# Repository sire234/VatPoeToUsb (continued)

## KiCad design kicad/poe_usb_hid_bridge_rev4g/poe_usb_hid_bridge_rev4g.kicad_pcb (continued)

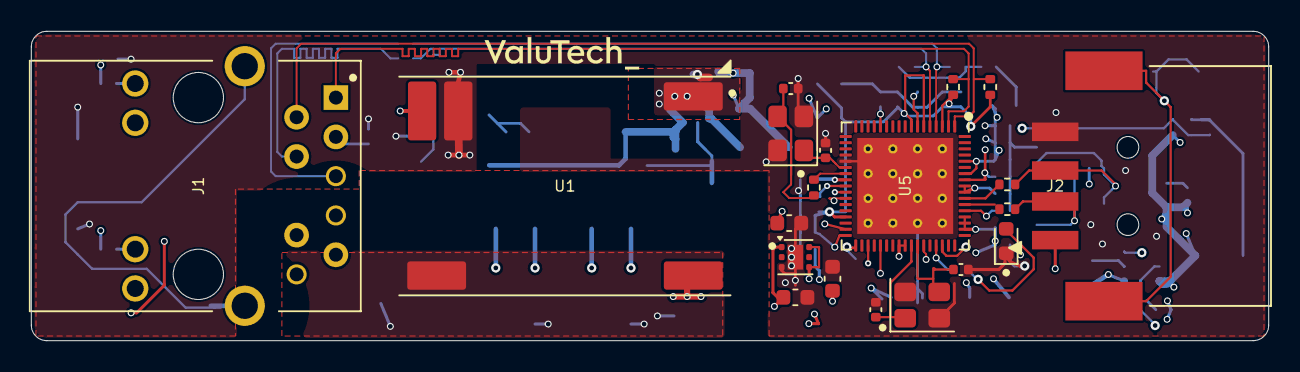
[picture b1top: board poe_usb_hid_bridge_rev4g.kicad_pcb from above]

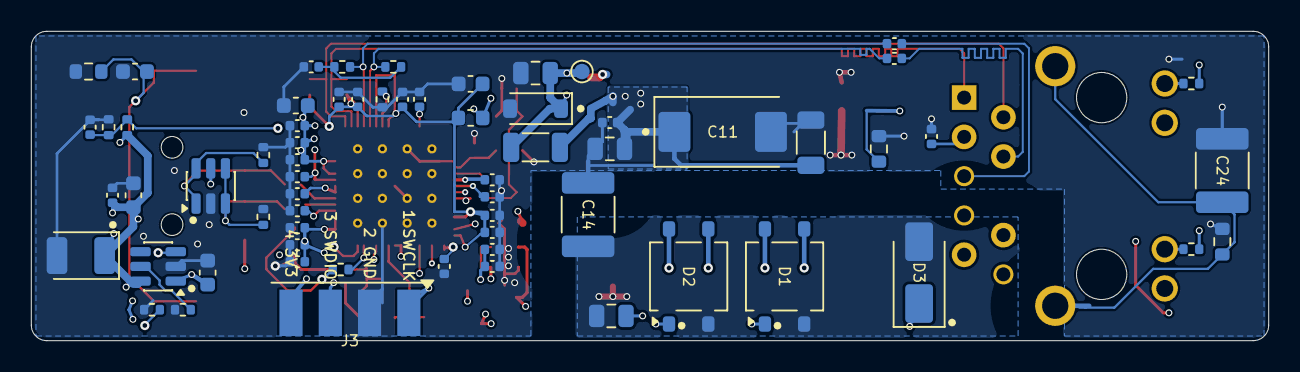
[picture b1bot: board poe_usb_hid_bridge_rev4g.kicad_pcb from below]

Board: 6 copper layers, 80.0 x 20.0 mm, 86 parts (65 on the bottom side), 46 nets.

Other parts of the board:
G1: Logo_ValuTech_10mm

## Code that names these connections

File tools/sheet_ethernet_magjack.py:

"""Wired layout of sheet B1 ethernet_magjack (HR871150C, TX/RX 49.9 R termination, RX coupling
caps C65/C66, CT decoupling, shield R7 || C24, PoE pairs to B2).
Usage: python tools/sheet_ethernet_magjack.py <source project dir (label-only rev4e)> <target project dir>
"""
from sheet_common import open_sheet, finish

s, dst = open_sheet('ethernet_magjack', 1, 'B1 ethernet_magjack – RJ45-MagJack HR871150C',
                    ['PHY-Seite (SEKUNDÄR, links): TX-Paar mit 49,9 Ω an +3V3A (R1/R2); CT an +3V3A (C23)',
                     'RX über Koppel-C C65/C66 6,8 nF (DC-Trennung, WIZnet-Referenz), Terminierung R3/R4 + C21',
                     'Kabelseite (PRIMÄR, rechts): J1.7–J1.10 → PSE_CT12/CT36/SP45/SP78 (zu B2); Schirm über R7 ∥ C24 an GND',
                     'MagJack-LEDs (Rev 4g): grün J1.13/14 = Link ← U5 LINKLED, gelb J1.11/12 = Activity ← U5 ACTLED,',
                     'aktiv low; Anoden über R5/R6 330 Ω an +3V3 (≈ 4 mA)'],
                    frame_size=(233.68, 157.48))

s.place('J1', 177.8, 88.9, 0, ref_at=(-10.16, -15.24), val_at=(-10.16, -12.7))
TXP, TXN, CT, RXP, RXN = 63.5, 71.12, 88.9, 109.22, 124.46
XL = 101.6                                   # left label column

# ---- fan-out of the PHY-side pins into widely spaced rows ----
tdp, tdm, ct = s.pin('J1', 'TD+'), s.pin('J1', 'TD-'), s.pin('J1', 'CT')
rdp, rdm = s.pin('J1', 'RD+'), s.pin('J1', 'RD-')
s.wire(tdp, (157.48, tdp[1]), (157.48, TXP), (XL, TXP))
s.wire(tdm, (154.94, tdm[1]), (154.94, TXN), (XL, TXN))
s.glabel('ETH_TXP', (XL, TXP), angle=180)
s.glabel('ETH_TXN', (XL, TXN), angle=180)

# TX termination: R1 TXP -> +3V3A (up), R2 TXN -> CT row (+3V3A)
s.place('R1', 137.16, TXP - 3.81, 0)
s.wire(s.pin('R1', '1'), (137.16, TXP - 10.16))
s.glabel('+3V3A', (137.16, TXP - 10.16), angle=90)
s.place('R2', 142.24, 77.47, 180)
s.wire((142.24, TXN), s.pin('R2', '2'))
s.wire(s.pin('R2', '1'), (142.24, CT))

# centre tap = +3V3A, decoupled by C23
s.wire(ct, (127.0, CT))
s.glabel('+3V3A', (127.0, CT), angle=180)
s.place('C23', 134.62, CT + 3.81, 0, ref_at=(-5.08, -1.27), val_at=(-5.08, 1.27))
s.power('GND', s.pin('C23', '2'), down=2.54)
s.flag((151.13, CT), up=2.54)

# RX: J1 -> coupling cap -> PHY, termination R3/R4 to ETH_RX_TERM, C21 to GND
s.wire(rdp, (154.94, rdp[1]), (154.94, RXP))
s.wire(rdm, (157.48, rdm[1]), (157.48, RXN))
s.place('C65', 144.78, RXP, 270, ref_at=(0, -3.81), val_at=(0, 3.81))
s.place('C66', 144.78, RXN, 270, ref_at=(0, -3.81), val_at=(0, 3.81))
s.wire((154.94, RXP), s.pin('C65', '1'))
s.wire((157.48, RXN), s.pin('C66', '1'))
s.wire((151.13, RXP), (151.13, RXP - 5.08))
s.glabel('ETH_RXP_J', (151.13, RXP - 5.08), angle=90)
s.wire((151.13, RXN), (151.13, RXN + 5.08))
s.glabel('ETH_RXN_J', (151.13, RXN + 5.08), angle=270)
s.wire(s.pin('C65', '2'), (XL, RXP))
s.wire(s.pin('C66', '2'), (XL, RXN))
s.glabel('ETH_RXP', (XL, RXP), angle=180)
s.glabel('ETH_RXN', (XL, RXN), angle=180)

s.place('R3', 127.0, RXP + 3.81, 0)
s.place('R4', 127.0, RXN - 3.81, 180)
term = s.pin('R3', '2')
s.place('C21', 113.03, term[1], 270, ref_at=(0, -3.81), val_at=(0, 3.81))
s.wire(term, s.pin('C21', '1'))
s.power('GND', s.pin('C21', '2'), left=2.54)
s.wire(term, (129.54, term[1]))
s.glabel('ETH_RX_TERM', (129.54, term[1]), angle=0)

# ---- cable side: PoE pairs to B2 ----
for pin, net in (('VC1+', 'PSE_CT12'), ('VC1-', 'PSE_CT36'), ('VC2+', 'PSE_SP45'), ('VC2-', 'PSE_SP78')):
    p = s.pin('J1', pin)
    s.wire(p, (205.74, p[1]))
    s.glabel(net, (205.74, p[1]), angle=0)

# ---- shield: R7 || C24 to GND ----
sh = s.pin('J1', 'SH')
s.place('R7', 190.5, 72.39, 0)
s.place('C24', 200.66, 72.39, 0)
s.wire(sh, (177.8, 68.58), (190.5, 68.58))
s.wire((190.5, 68.58), (200.66, 68.58), (210.82, 68.58))
s.glabel('SHIELD_RJ45', (210.82, 68.58), angle=0)
s.power('GND', s.pin('R7', '2'), down=2.54)
s.power('GND', s.pin('C24', '2'), down=2.54)

# ---- MagJack LEDs (Rev 4g): cathodes to U5 LINKLED/ACTLED, anodes via R5/R6 to +3V3 ----
s.add_lib_symbol(r'C:\Program Files\KiCad\10.0\share\kicad\symbols\power.kicad_sym', '+3V3', 'power')
for ref in ('R5', 'R6'):
    s.new_comp(ref, 'Device:R', '330R', 'Resistor_SMD:R_0402_1005Metric',
               [('MPN', '0402WGF3300TCE'), ('LCSC', 'C25104')])
# rows below J1, rightmost pin takes the top row (no crossings)
for pin, row, kind, net, rref in (('14', 104.14, 'K', 'ETH_LED_LINK_N', None),
                                  ('13', 114.3, 'A', 'ETH_LED_LINK_A', 'R6'),
                                  ('12', 124.46, 'K', 'ETH_LED_ACT_N', None),
                                  ('11', 134.62, 'A', 'ETH_LED_ACT_A', 'R5')):
    p = s.pin('J1', pin)
    if kind == 'K':
        s.wire(p, (p[0], row), (185.42, row))
        s.glabel(net, (185.42, row), angle=0)
    else:
        s.place(rref, 205.74, row - 3.81, 180)         # pin 1 (anode) on the row, pin 2 up to +3V3
        s.wire(p, (p[0], row), (215.9, row))
        s.glabel(net, (215.9, row), angle=0)
        s.power('+3V3', s.pin(rref, '2'), up=0)

finish(s, dst)

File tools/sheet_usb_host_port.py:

"""Wired layout of sheet B6 usb_host_port (TPS2553 switch, VBUS caps + sense divider,
27 R series resistors, USBLC6 ESD, USB-A J2, shield R34/C30).
Usage: python tools/sheet_usb_host_port.py <source project dir (label-only rev4e)> <target project dir>
"""
from sheet_common import open_sheet, finish

s, dst = open_sheet('usb_host_port', 6, 'B6 usb_host_port – USB-A-Host',
                    ['TPS2553 Lastschalter (R25 44,2 k → 532–659 mA), FAULT offen; VBUS-Teiler R32/R33 → VBUS_SENSE (Faktor 0,405)',
                     'USB-Daten: 27-Ω-Serien-R R28/R29 → USBLC6 ESD → J2;  R30/R31 (15 k) und C30 DNP'],
                    frame_size=(269.24, 144.78))

# ---------------- power path: +5V -> U6 -> VBUS_USB -> J2 ----------------
s.place('U6', 101.6, 76.2, 0, ref_at=(0, -8.89), val_at=(0, -6.35))
s.place('C17', 53.34, 77.47, 0, ref_at=(-5.08, -1.27), val_at=(-5.08, 1.27))
s.place('R26', 81.28, 80.01, 0, ref_at=(-5.08, -1.27), val_at=(-5.08, 1.27))
s.place('R25', 86.36, 90.17, 0)
s.place('J2', 241.3, 80.01, 0, mirror='y', ref_at=(0, -11.43), val_at=(0, -8.89))

vin = s.power('+5V', (45.72, 73.66))
s.wire(vin, s.pin('U6', 'IN'))
s.power('GND', s.pin('C17', '2'), down=2.54)

en = s.pin('U6', 'EN')
s.wire(en, (73.66, en[1]))
s.glabel('USB_EN', (73.66, en[1]), angle=180)
s.power('GND', s.pin('R26', '2'), down=2.54)

ilim = s.pin('U6', 'ILIM')
s.wire(ilim, (86.36, ilim[1]), s.pin('R25', '1'))
s.glabel('ILIM_SET', s.pin('R25', '1'), angle=0)
s.power('GND', s.pin('R25', '2'), down=2.54)
s.power('GND', s.pin('U6', 'GND'), down=3.81)
s.noconnect(s.pin('U6', 'FAULT'))

vbus_y = s.pin('U6', 'OUT')[1]
s.wire(s.pin('U6', 'OUT'), s.pin('J2', 'VBUS'))
s.wire((116.84, vbus_y), (116.84, vbus_y - 5.08))
s.glabel('VBUS_USB', (116.84, vbus_y - 5.08), angle=90)
for ref, x in (('C18', 124.46), ('C19', 137.16), ('C20', 149.86)):
    s.place(ref, x, vbus_y + 3.81, 0)
    s.power('GND', s.pin(ref, '2'), down=2.54)

# VBUS sense divider R32/R33 with filter C29
s.place('R32', 162.56, vbus_y + 3.81, 0)
s.place('R33', 162.56, vbus_y + 11.43, 0)
s.place('C29', 175.26, vbus_y + 11.43, 0)
node = s.pin('R32', '2')
s.wire(node, s.pin('C29', '1'), (180.34, node[1]))
s.glabel('VBUS_SENSE', (180.34, node[1]), angle=0)
s.power('GND', s.pin('R33', '2'), down=2.54)
s.power('GND', s.pin('C29', '2'), down=2.54)

# ---------------- data path: MCU -> 27 R -> USBLC6 -> J2 ----------------
dp_y, dm_y = 105.41, 120.65
s.place('R28', 91.44, dp_y, 90)
s.place('R29', 91.44, dm_y, 90)
s.place('R30', 106.68, dp_y + 3.81, 0)
s.place('R31', 106.68, dm_y + 3.81, 0)
s.place('U7', 200.66, dp_y, 0, ref_at=(7.62, -6.35), val_at=(7.62, -3.81))

s.wire(s.pin('R28', '1'), (76.2, dp_y))
s.glabel('USB_DP_MCU', (76.2, dp_y), angle=180)
s.wire(s.pin('R29', '1'), (76.2, dm_y))
s.glabel('USB_DM_MCU', (76.2, dm_y), angle=180)

io1_l, io2_l = s.pin('U7', '1'), s.pin('U7', '3')
s.wire(s.pin('R28', '2'), io1_l)
s.wire(s.pin('R29', '2'), (190.5, dm_y), (190.5, io2_l[1]), io2_l)
s.wire((99.06, dp_y), (99.06, dp_y - 5.08))
s.glabel('USB_DP', (99.06, dp_y - 5.08), angle=90)
s.wire((99.06, dm_y), (99.06, dm_y + 5.08))
s.glabel('USB_DM', (99.06, dm_y + 5.08), angle=270)
s.power('GND', s.pin('R30', '2'), down=2.54)
s.power('GND', s.pin('R31', '2'), down=2.54)

vb = s.pin('U7', 'VBUS')
s.wire(vb, (vb[0], vbus_y))                      # straight up to the VBUS rail
s.power('GND', s.pin('U7', 'GND'), down=2.54)

io1_r, io2_r = s.pin('U7', '6'), s.pin('U7', '4')
jdp, jdm = s.pin('J2', 'D+'), s.pin('J2', 'D-')
s.wire(io1_r, (220.98, io1_r[1]), (220.98, jdp[1]), jdp)
s.wire(io2_r, (223.52, io2_r[1]), (223.52, jdm[1]), jdm)
# USBLC6 I/O pins 1/6 and 3/4 are separate symbol pins of the same net -> label both sides
s.wire((213.36, io1_r[1]), (213.36, io1_r[1] - 5.08))
s.glabel('USB_DP', (213.36, io1_r[1] - 5.08), angle=90)
s.wire((215.9, io2_r[1]), (215.9, io2_r[1] + 5.08))
s.glabel('USB_DM', (215.9, io2_r[1] + 5.08), angle=270)

# ---------------- connector ground and shield ----------------
s.power('GND', s.pin('J2', 'GND'), down=2.54)
sh = s.pin('J2', 'SH')
s.place('R34', sh[0], sh[1] + 8.89, 0, ref_at=(-5.08, -1.27), val_at=(-5.08, 1.27))
s.place('C30', sh[0] + 7.62, sh[1] + 8.89, 0)
tap = (sh[0], sh[1] + 2.54)
s.wire(sh, s.pin('R34', '1'))
s.wire(tap, (sh[0] + 7.62, tap[1]), s.pin('C30', '1'))
s.wire((sh[0] + 7.62, tap[1]), (sh[0] + 12.7, tap[1]))
s.glabel('USB_SHIELD', (sh[0] + 12.7, tap[1]), angle=0)
s.power('GND', s.pin('R34', '2'), down=2.54)
s.power('GND', s.pin('C30', '2'), down=2.54)

finish(s, dst)

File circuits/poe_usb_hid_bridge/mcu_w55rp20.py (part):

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Block from: architecture/net_plan.md section 8 "B5"
Interface nets: +3V3, +3V3A, GND, ETH_TXP, ETH_TXN, ETH_RXP, ETH_RXN, USB_DP_MCU, USB_DM_MCU, USB_EN, VBUS_SENSE, LED_DIN,
                ETH_LED_LINK_N, ETH_LED_ACT_N
Rev 4b: RGB GPIOs reduced to one line LED_DIN = GPIO28 (pin 48), GPIO27 (47) and GPIO19 (41) NC.
Rev 4f: LED_DIN drives the plain green status LED D11 (name kept from the WS2812 design).
Rev 4g: W5500 LED outputs 37 LINKLED / 39 ACTLED drive the MagJack LEDs (Rev 4b-4f: NC).
Rev 4d (based on Rev 4b, Rev-4c bridges/pads NOT taken over):
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        eth_txp, eth_txn: Ethernet TX differential pair to the MagJack
        eth_rxp, eth_rxn: Ethernet RX differential pair from the MagJack
        usb_dp_mcu, usb_dm_mcu: RP2040 USB D+/D- (to series resistors in B6)
        usb_en: GPIO26 -> USB power switch enable
        vbus_sense: GPIO29/ADC3 <- VBUS divider
        led_din: GPIO28 (pin 48) -> green status LED D11 via R38 (Rev 4f, high = on)
        eth_led_link_n: W5500 LINKLED (pin 37, low = link) -> MagJack green LED cathode
        eth_led_act_n: W5500 ACTLED (pin 39, low = activity) -> MagJack yellow LED cathode
    """
    # ------------------------------------------------------------------
    # Internal nets (names per net_plan section 8 B5)
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    u5[28] += swdio

    # Application GPIO
    u5[46] += usb_en            # GPIO26/ADC0
    u5[48] += led_din           # GPIO28/ADC2 -> green status LED (Rev 4f)
    u5[49] += vbus_sense        # GPIO29/ADC3
    u5[57] += usb_dm_mcu
    u5[58] += usb_dp_mcu

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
